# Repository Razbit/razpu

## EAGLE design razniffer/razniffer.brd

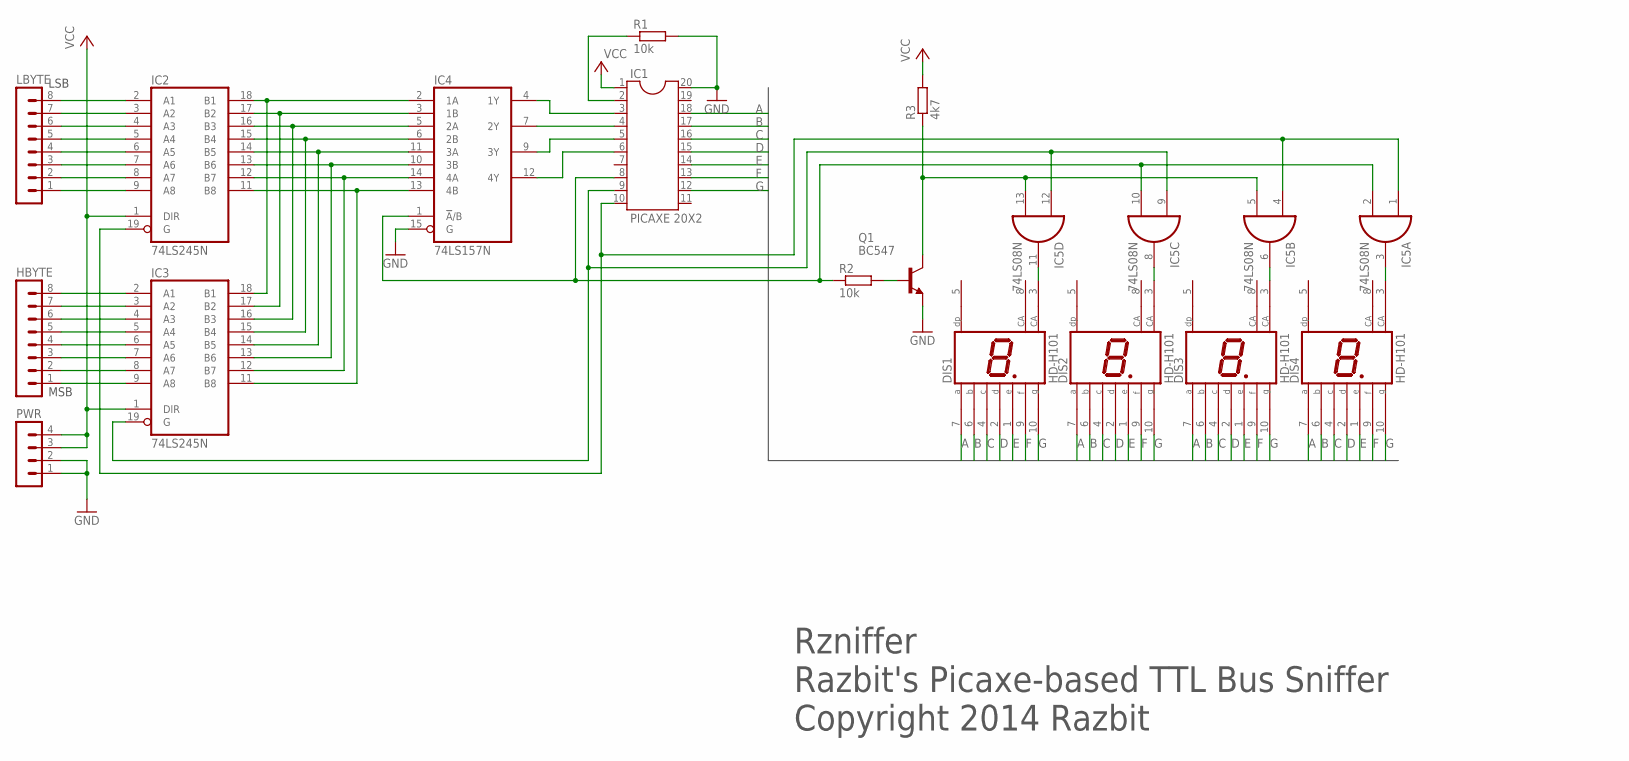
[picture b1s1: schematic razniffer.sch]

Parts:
DIS1, DIS2, DIS3, DIS4: HD-H101; HDSP-M
HBYTE: MA08-1
IC1: PICAXE 20X2; DIL20
IC2, IC3: 74LS245N; DIL20
IC4: 74LS157N; DIL16
IC5: 74LS08N; DIL14
LBYTE: MA08-1
PWR: MA04-1
Q1: BC547; TO92
R1, R2: 10k; 0204/7
R3: 4k7; 0204/7

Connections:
A: DIS1.7 (A), DIS2.7 (A), DIS3.7 (A), DIS4.7 (A), IC1.18
B: DIS1.6 (B), DIS2.6 (B), DIS3.6 (B), DIS4.6 (B), IC1.17
C: DIS1.4 (C), DIS2.4 (C), DIS3.4 (C), DIS4.4 (C), IC1.16
D: DIS1.2 (D), DIS2.2 (D), DIS3.2 (D), DIS4.2 (D), IC1.15
E: DIS1.1 (E), DIS2.1 (E), DIS3.1 (E), DIS4.1 (E), IC1.14
F: DIS1.9 (F), DIS2.9 (F), DIS3.9 (F), DIS4.9 (F), IC1.13
G: DIS1.10 (G), DIS2.10 (G), DIS3.10 (G), DIS4.10 (G), IC1.12
GND: IC1.20, IC2.10 (GND), IC3.10 (GND), IC4.8 (GND), IC4.15 (G), IC5.7 (GND), PWR.1, PWR.2, Q1.1 (E), R1.2
unnamed: IC2.2 (A1), LBYTE.8
unnamed: IC2.3 (A2), LBYTE.7
unnamed: IC2.4 (A3), LBYTE.6
unnamed: IC2.5 (A4), LBYTE.5
unnamed: IC2.6 (A5), LBYTE.4
unnamed: IC2.7 (A6), LBYTE.3
unnamed: IC2.8 (A7), LBYTE.2
unnamed: IC2.9 (A8), LBYTE.1
unnamed: HBYTE.8, IC3.2 (A1)
unnamed: HBYTE.7, IC3.3 (A2)
unnamed: HBYTE.6, IC3.4 (A3)
unnamed: HBYTE.5, IC3.5 (A4)
unnamed: HBYTE.4, IC3.6 (A5)
unnamed: HBYTE.3, IC3.7 (A6)
unnamed: HBYTE.2, IC3.8 (A7)
unnamed: HBYTE.1, IC3.9 (A8)
unnamed: IC5.5 (I1), IC5.13 (I1), Q1.3 (C), R3.1
unnamed: IC2.18 (B1), IC3.18 (B1), IC4.2 (1A)
unnamed: IC2.17 (B2), IC3.17 (B2), IC4.3 (1B)
unnamed: IC2.16 (B3), IC3.16 (B3), IC4.5 (2A)
unnamed: IC2.15 (B4), IC3.15 (B4), IC4.6 (2B)
unnamed: IC2.14 (B5), IC3.14 (B5), IC4.11 (3A)
unnamed: IC2.13 (B6), IC3.13 (B6), IC4.10 (3B)
unnamed: IC2.12 (B7), IC3.12 (B7), IC4.14 (4A)
unnamed: IC2.11 (B8), IC3.11 (B8), IC4.13 (4B)
unnamed: Q1.2 (B), R2.2
unnamed: IC1.2, R1.1
unnamed: IC1.3, IC4.4 (1Y)
unnamed: IC1.4, IC4.7 (2Y)
unnamed: IC1.5, IC4.9 (3Y)
unnamed: IC1.6, IC4.12 (4Y)
unnamed: IC1.10, IC2.19 (G), IC5.1 (I0), IC5.4 (I0)
unnamed: IC1.9, IC3.19 (G), IC5.9 (I0), IC5.12 (I0)
unnamed: IC1.8, IC4.1 (!A!/B), IC5.2 (I1), IC5.10 (I1), R2.1
unnamed: DIS1.3 (CA), IC5.11 (O)
unnamed: DIS2.3 (CA), IC5.8 (O)
unnamed: DIS3.3 (CA), IC5.6 (O)
unnamed: DIS4.3 (CA), IC5.3 (O)
VCC: IC1.1, IC2.1 (DIR), IC2.20 (VCC), IC3.1 (DIR), IC3.20 (VCC), IC4.16 (VCC), IC5.14 (VCC), PWR.3, PWR.4, R3.2

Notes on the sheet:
Rzniffer Razbit's Picaxe-based TTL Bus Sniffer Copyright 2014 Razbit
LSB
MSB

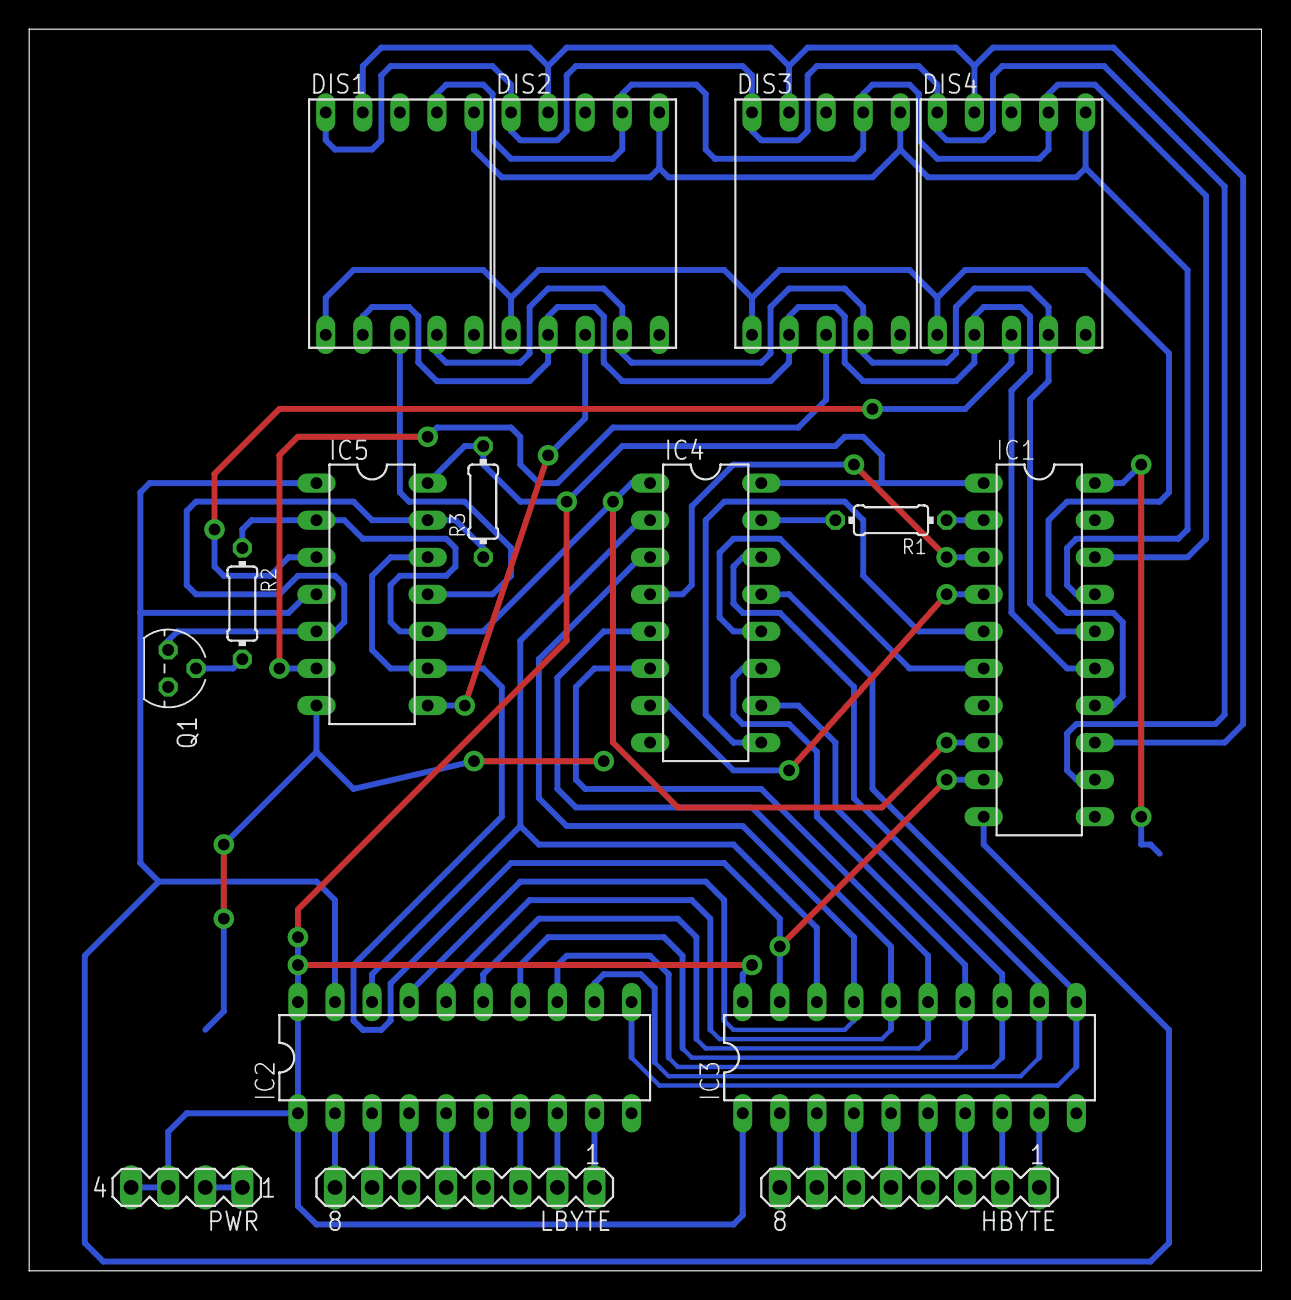
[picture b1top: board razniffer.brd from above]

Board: 2 copper layers, 84.4 x 85.1 mm, 16 parts (0 on the bottom side), 47 nets.
